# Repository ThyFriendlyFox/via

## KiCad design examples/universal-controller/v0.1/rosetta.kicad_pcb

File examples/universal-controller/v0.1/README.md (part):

# Rosetta v0.1: a universal game controller

Archived: [v0.2](../v0.2/README.md) is current. It is laid out like an Xbox 360 controller's main
board, with the thumbsticks, the Hall-effect triggers and the bumpers on it.

One controller for a PS4, a PS5, an Xbox, a Switch, or anything over Bluetooth. A 5-position
knob on its face picks the console. The controller drops off the bus while the knob turns and
comes back as the chosen console's own controller.

This folder is a whole KiCad 10 project made with Via: `design.py` is the board, and the
`.kicad_*` files beside it are what `workcenter design` writes from it. It is Via's example
project, laid out the way a board repository lays out a version.

<!-- pictures:begin -->

| Front | Back |
|---|---|
|  |  |

| Every layer | The schematic, wired, in blocks |
|---|---|
|  |  |

From `workcenter render . --strict --views schematic,3d,layers,spin --width 1600 --spin-zoom 1.1`, with
KiCad's 3D bodies in `KICAD10_3DMODEL_DIR` (Via's `site/media/README.md` says how to
fetch them) and the 3 bodies in `models/`.
<!-- pictures:end -->

## What is hard about it, and where each part lives

| The problem | The answer on this board |
|---|---|
| 1 knob, 5 consoles, no microcontroller pin to spare | SW1, an NKK NR01 1-pole 5-position rotary switch, taps a ladder of 6 x 1k (R40-R45). The ADC reads 1 number: position k at (6 - k)/6 of full scale. Between detents R46 (100k) pulls the wiper to ~0, and the firmware drops off the bus. 6 decks hold every position inside its window at every corner (`sim/`). |
| A PS4, a PS5 and an Xbox talk only to a licensed controller | J2 is a USB host port for an auth donor: a licensed controller or dongle. The RP2040 runs a second USB port in software (PIO-USB, GPIO16 and GPIO17, R7 to R10) and relays the console's challenge to the donor. U13 switches the port's 5 V and reports a fault. |
| Bluetooth Classic (the Switch, PlayStation pads) and BLE (phones, PCs) | U3, an ESP32-WROOM-32E, on the RP2040's UART0. The RP2040 holds its EN and IO0, so it can put the ESP32 in its bootloader and flash it: 1 USB cable updates both chips. U3 sits on the back, turned so its antenna hangs past the notch between the grips: the footprint's antenna keep-out lies in the air. |
| Sticks that drift | Hall-effect stick and trigger modules on J3 to J6, read by U4, a 12-bit 8-input SPI ADC (MCP3208) whose reference is the same +3V3 that feeds the sensors. |
| Triggers that push back (the PS5's trigger effects) | A small motor in each trigger module, on pins 4 and 5 of J3 and J4, driven both ways by U6 (DRV8833). |
| Rumble in each grip | An LRA on J7 and J8, each with a DRV2605L (U9, U10). The chip has 1 fixed I2C address, so each has its own bus (I2C0, I2C1). |
| Gyro aim | U5, an LSM6DSL 6-axis IMU on I2C0. |
| A light that names the console | 5 RGB LEDs (D2-D6, WS2812B-2020) on a ring round the knob. They need 3.7 V or more; they run from VSYS (the cell or USB), and U14 (74AHCT1G125) lifts the RP2040's 3.3 V data to that rail. |
| 16 buttons and 2 paddles | 2 74HC165 shift registers (U7, U8) on 3 pins, each input held up by a 10k in a pack (RN1-RN4). The back paddles SW15 and SW16 go to their own pins. |

## The board

- Outline: a controller's silhouette, 160 x 92 mm, drawn in `design.py` as a polygon with filleted
  corners (`ControllerDesign`). The notch between the grips is concave; its edge is where the
  ESP32's antenna hangs out.
- 4 layers, 1.6 mm: F.Cu signal, In1.Cu a whole GND plane, In2.Cu signal, B.Cu signal. Order it as
  4 layers.
- The front carries what a hand touches: the D-pad, A/B/X/Y, L1/R1, Share, Options, Home,
  Capture, the knob and its ring, and the connectors. The back carries the electronics and the
  2 paddles.
- 2 stick modules sit over the face at (147, 141) and (193, 141): `design.py` keeps every part on
  the front out of a 10 mm circle there (`d.keepout(..., parts=True, copper=False)`).

### Power

USB VBUS (J1) feeds VSYS through D1; with no cable, Q1 (AO3401A) connects the cell to VSYS. Its
gate sits on VBUS, held low by R13 when the cable is out. U11 (MCP73831) charges the cell at
500 mA (R12, 2k). U12 (AP7361C, 1 A) makes +3V3 from VSYS. The RP2040 makes its own +1V1. R14 and
R15 halve the cell's voltage for the ADC (channel 7).

### The RP2040's pins

| GPIO | Net | To |
|---|---|---|
| 0, 1 | ESP_RXD, ESP_TXD | U3 UART0 (pins 34, 35) |
| 2, 3 | ESP_EN, ESP_IO0 | U3 reset and boot strap, each pulled up (R20, R21) |
| 4, 5 | I2C0 | U5 IMU, U9 left haptics, R26/R27 |
| 6, 7 | I2C1 | U10 right haptics, R28/R29 |
| 8-11 | ADC_MISO, ADC_CS, ADC_SCK, ADC_MOSI | U4 (SPI1); R22 holds CS high in reset |
| 12, 13, 14 | SR_PL, SR_CLK, SR_Q | U7, U8 (R47, R48 hold the load and clock in reset) |
| 15 | LED_DATA | U14, then the ring (R49 holds it low in reset) |
| 16, 17 | PIO_D+, PIO_D- | J2 through R7, R8 (PIO-USB host; R9, R10 the host's pull-downs) |
| 18, 19 | HOST_EN, FAULT_N | U13 enable (R11 off in reset); U13's and U6's faults, wired-OR (R24) |
| 20-23 | TRIG_L_A/B, TRIG_R_A/B | U6 inputs, PWM slices 2 and 3 |
| 24 | MOT_SLEEP | U6 nSLEEP (R23 low in reset) |
| 25 | IMU_INT | U5 INT1 |
| 26 | HAPTIC_EN | U9, U10 EN (R25 low in reset) |
| 27, 28 | PADDLE_L, PADDLE_R | SW15, SW16 (internal pull-ups) |
| 29 | CHG_STAT | U11 STAT (internal pull-up) |

The ADC's channels: 0-3 the sticks' X and Y, 4 and 5 the triggers, 6 the knob, 7 the cell.

### Connectors

| Ref | Part | Pins |
|---|---|---|
| J1 | USB-C (GCT USB4085, through-hole) to the console | VBUS, D+/D- (R3, R4 27 ohm), CC1/CC2 5.1k to GND (a device) |
| J2 | USB-C to the auth donor | VBUS_HOST from U13, D+/D- to PIO-USB, CC1/CC2 56k to VBUS_HOST (a source) |
| J3, J4 | JST SH 5-way, left and right trigger modules | 1 +3V3, 2 Hall output, 3 GND, 4 and 5 the motor |
| J5, J6 | JST SH 5-way, left and right stick modules | 1 +3V3, 2 X, 3 Y, 4 the stick's click, 5 GND |
| J7, J8 | JST SH 2-way, the LRAs | 1 OUT+, 2 OUT- |
| J9 | JST PH 2-way, the cell | 1 BAT, 2 GND |
| J10 | JST SH 3-way, Raspberry Pi's debug connector, on the back | 1 SWCLK, 2 GND, 3 SWDIO |

## What proves it

```sh
workcenter design design.py --route    # the KiCad project, routed: from this folder
workcenter gates .                     # ERC, DRC, SIM, EXPORT
make -C firmware test                  # the knob's decoder on the host
```

- **The gates.** ERC and DRC on the routed board, the 6 knob decks at their corners, and the
  fabrication outputs in `build/fab/`. The site shows the run.
- **The knob, simulated.** `sim/mode_p1.cir` to `sim/mode_p5.cir` put the wiper on each tap and
  `sim/mode_between.cir` on none, each with the ADC's worst input leakage (1 uA). Every resistor
  runs at both ends of 1 % and 32 Monte Carlo draws (`sim/corners.json`). Each position stays
  within 0.04 of full scale of its nominal; the decoder's thresholds are 0.0833 away.
  The first value of R46 was 1 M: with that leakage it read 1 V between detents, a position.
  The deck found it; R46 is 100k and the ladder 1k.
- **The decoder.** `firmware/src/mode.c` turns a reading into a mode and decides when to drop off
  the bus and come back. `firmware/tests/test_mode.c` checks it against the decks' corner values:
  a brush past a tap changes nothing, and a fast flick detaches before it attaches.

## Parts and why

| Ref | Part | Why |
|---|---|---|
| U1 | RP2040, W25Q128JV (U2), 12 MHz (Y1) | Native USB for the console, PIO for a second USB port in software, 2 I2C, 2 UART, SPI, 16 PWM channels. |
| U3 | ESP32-WROOM-32E | Bluetooth Classic and BLE in 1 certified module. The ESP32-S3 has BLE only. |
| U4 | MCP3208 | 8 inputs at 12 bits on SPI, against an external reference. |
| U5 | LSM6DSL | A 6-axis IMU in KiCad's library, I2C. |
| U6 | DRV8833 | 2 H-bridges for the 2 trigger motors, from VSYS. |
| U9, U10 | DRV2605L | LRA drivers with a library of effects and auto-resonance. |
| U11 | MCP73831 | A 1-cell charger in SOT-23-5. |
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
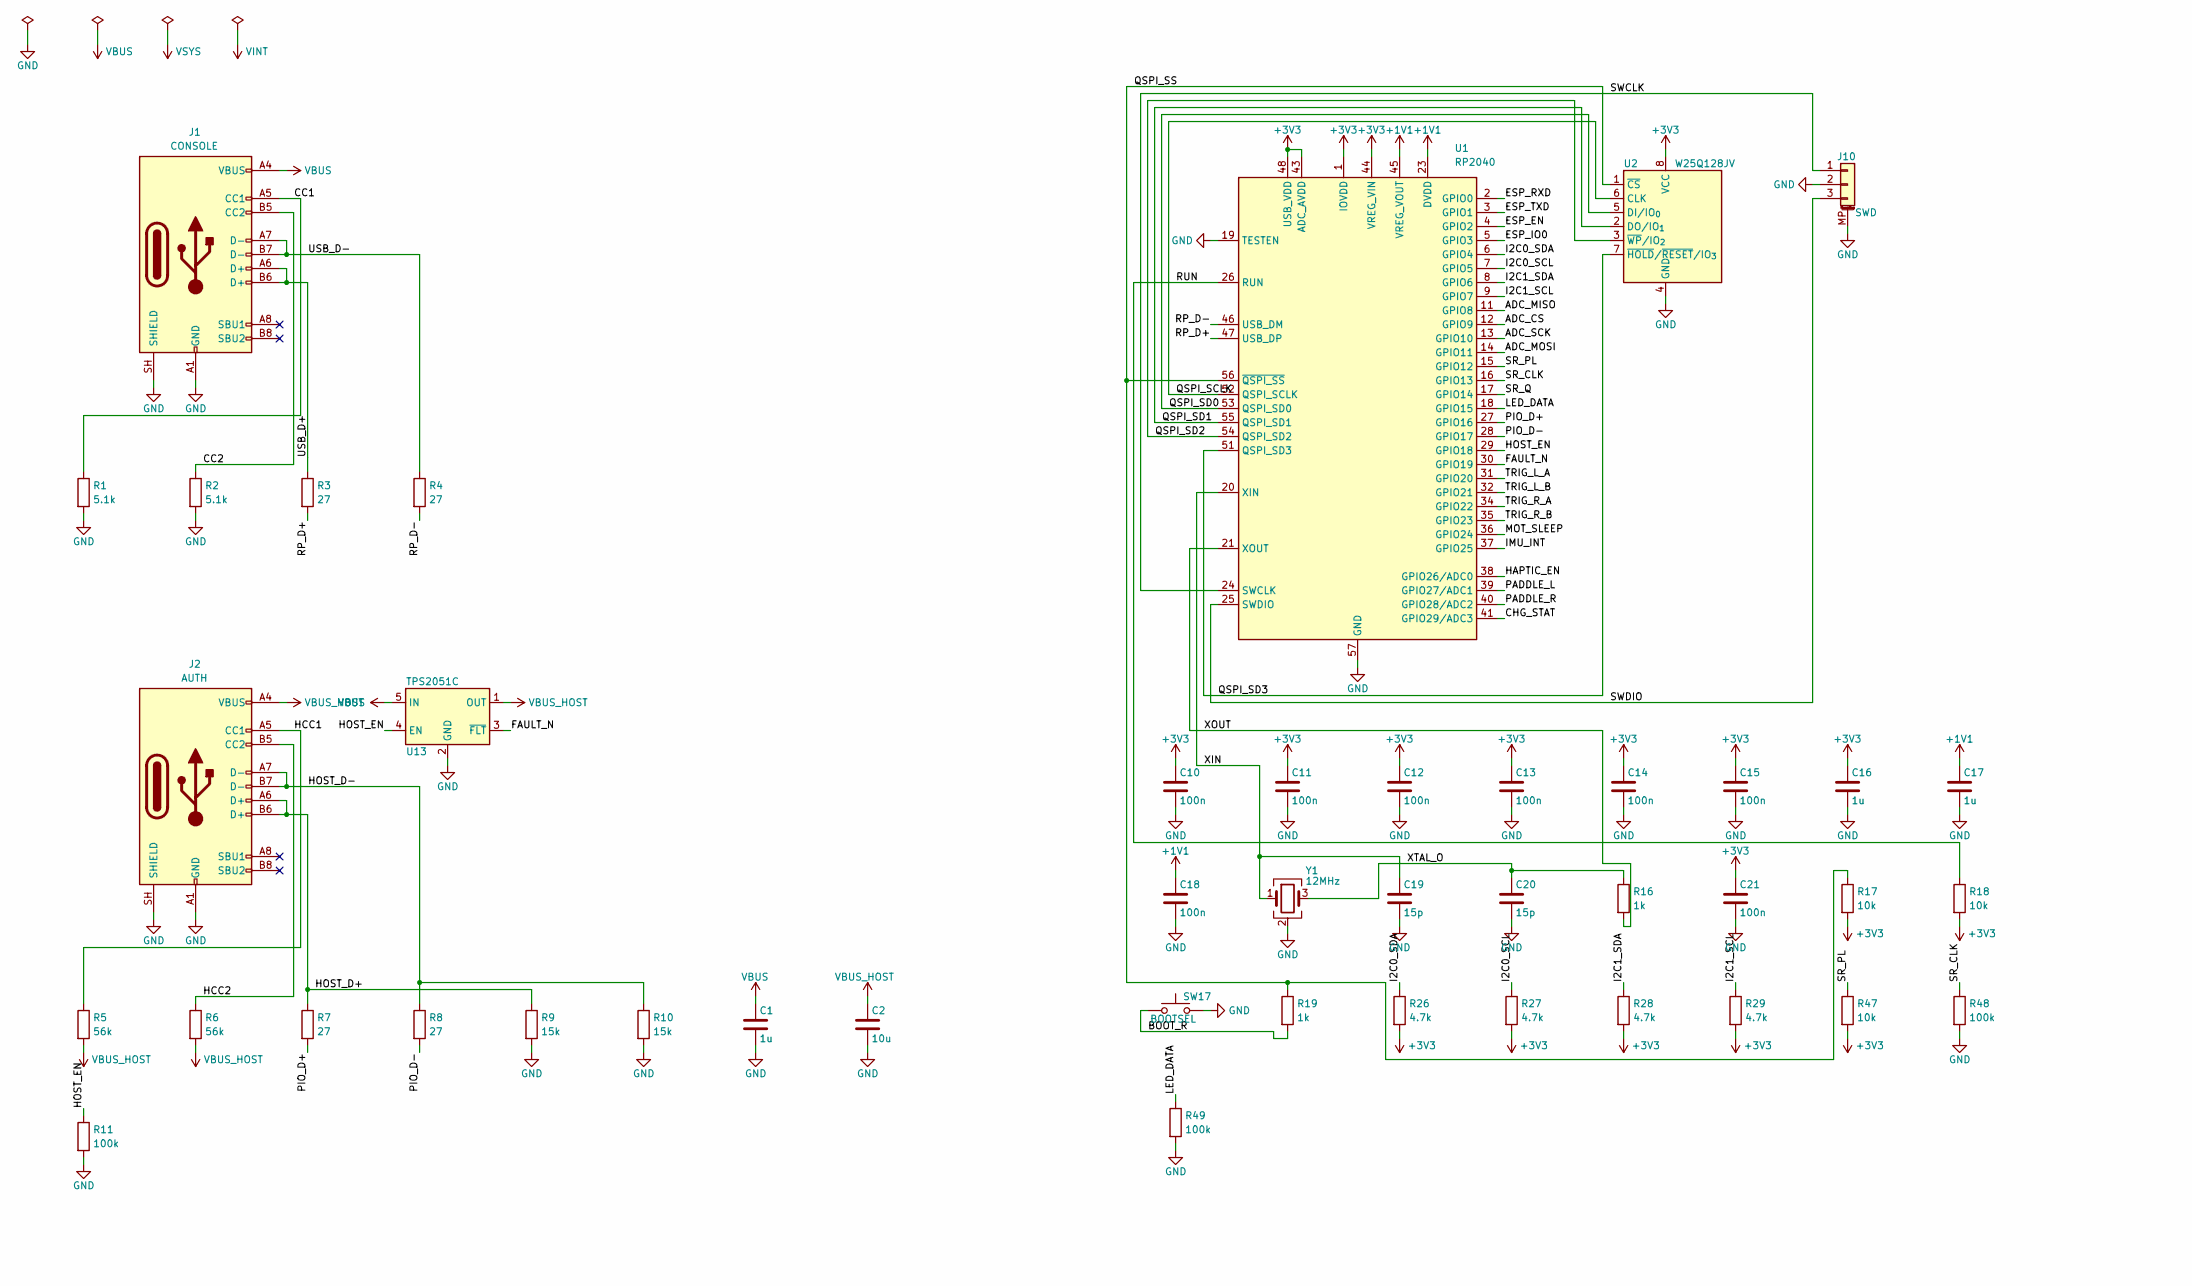
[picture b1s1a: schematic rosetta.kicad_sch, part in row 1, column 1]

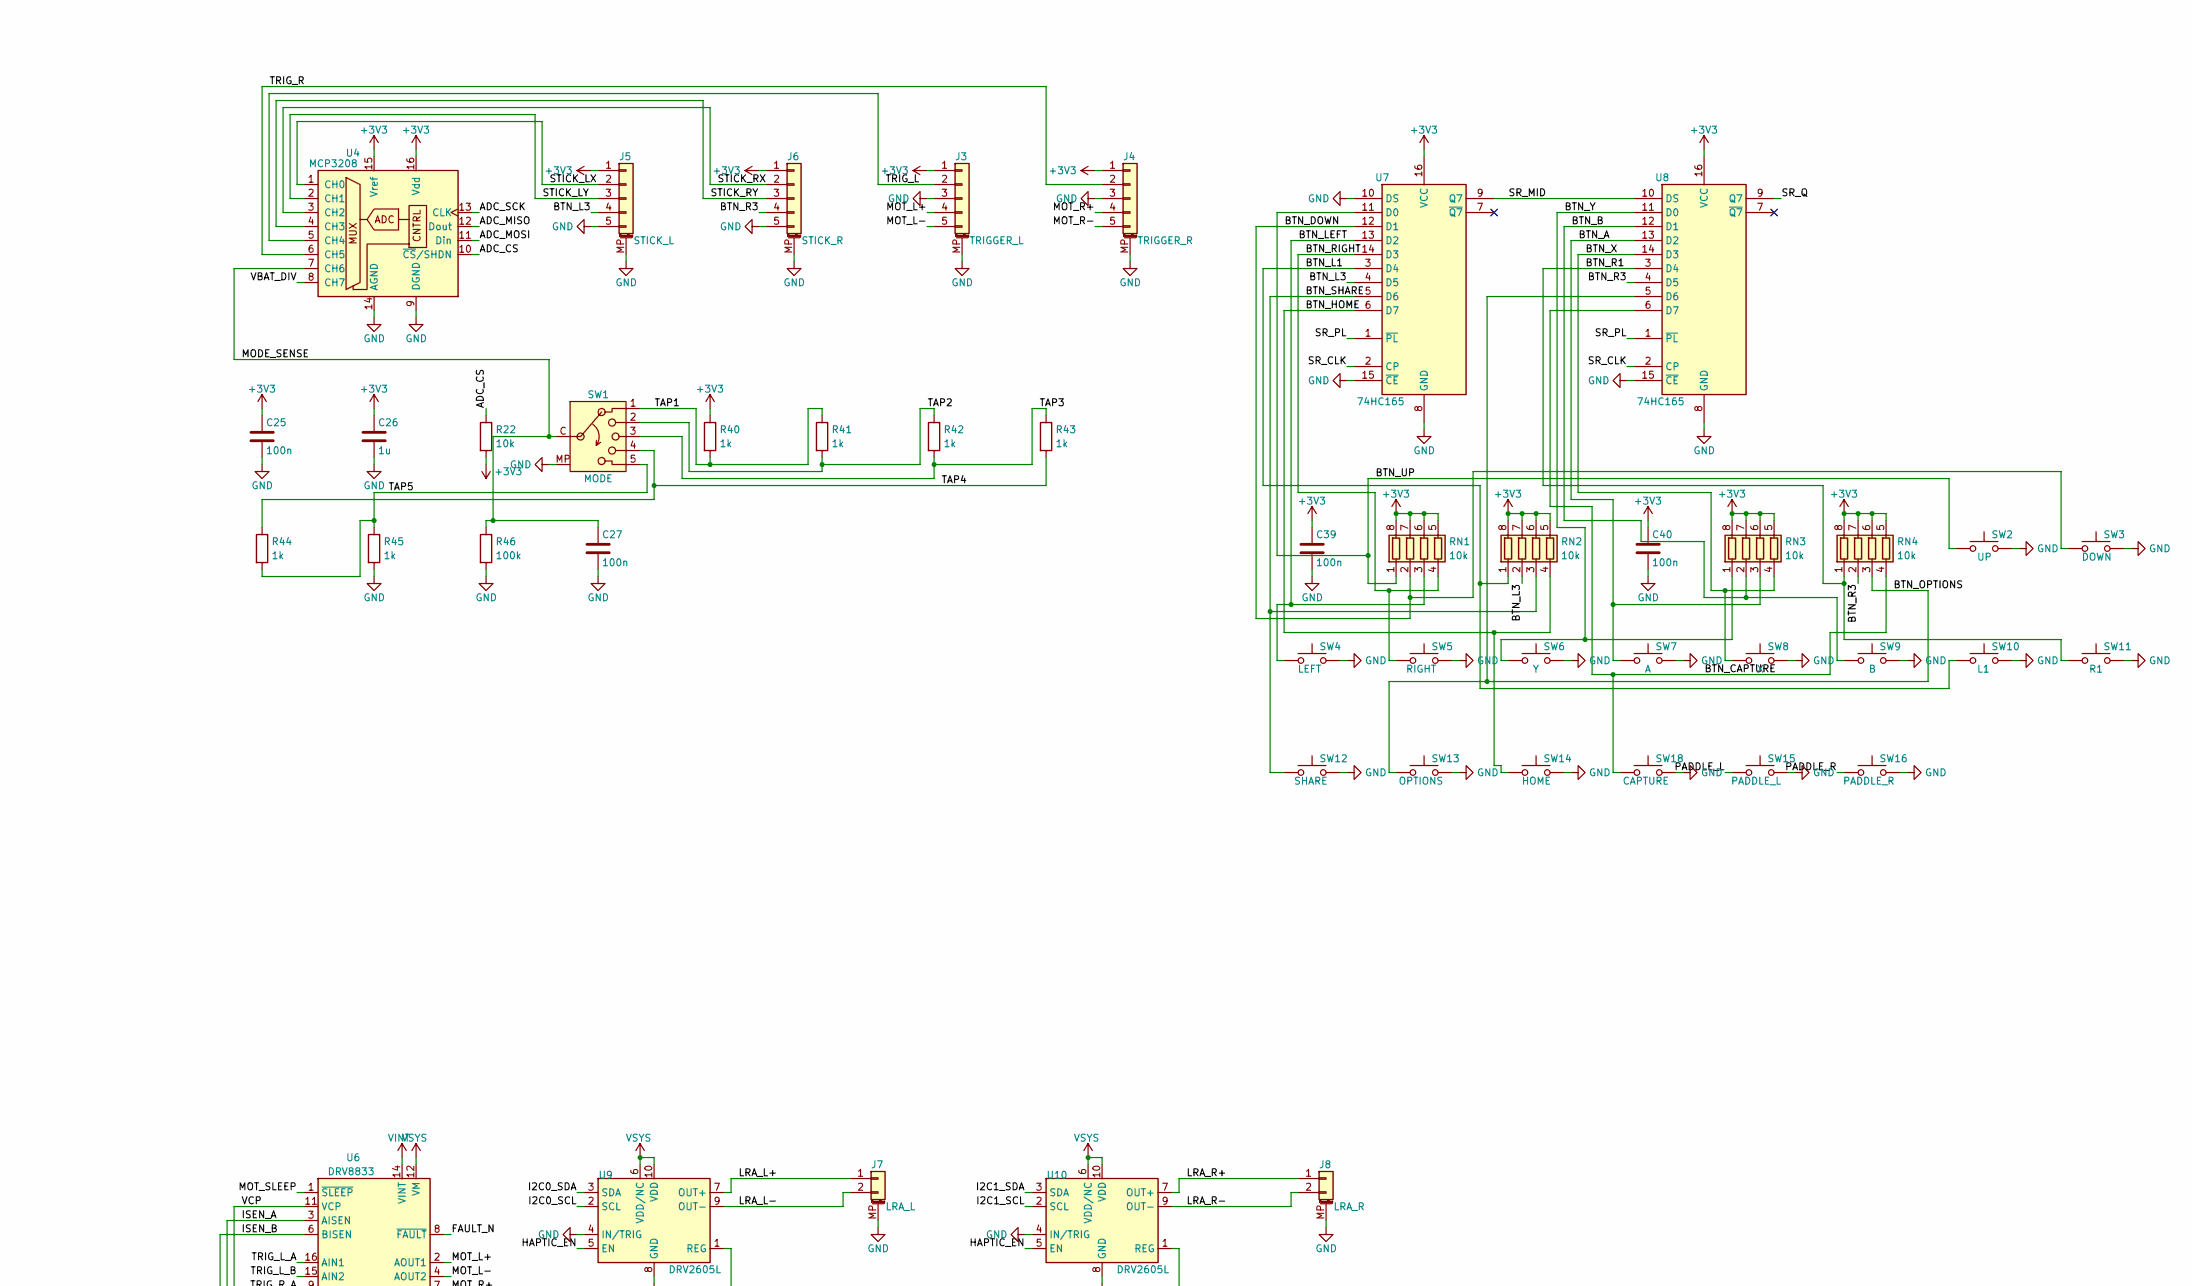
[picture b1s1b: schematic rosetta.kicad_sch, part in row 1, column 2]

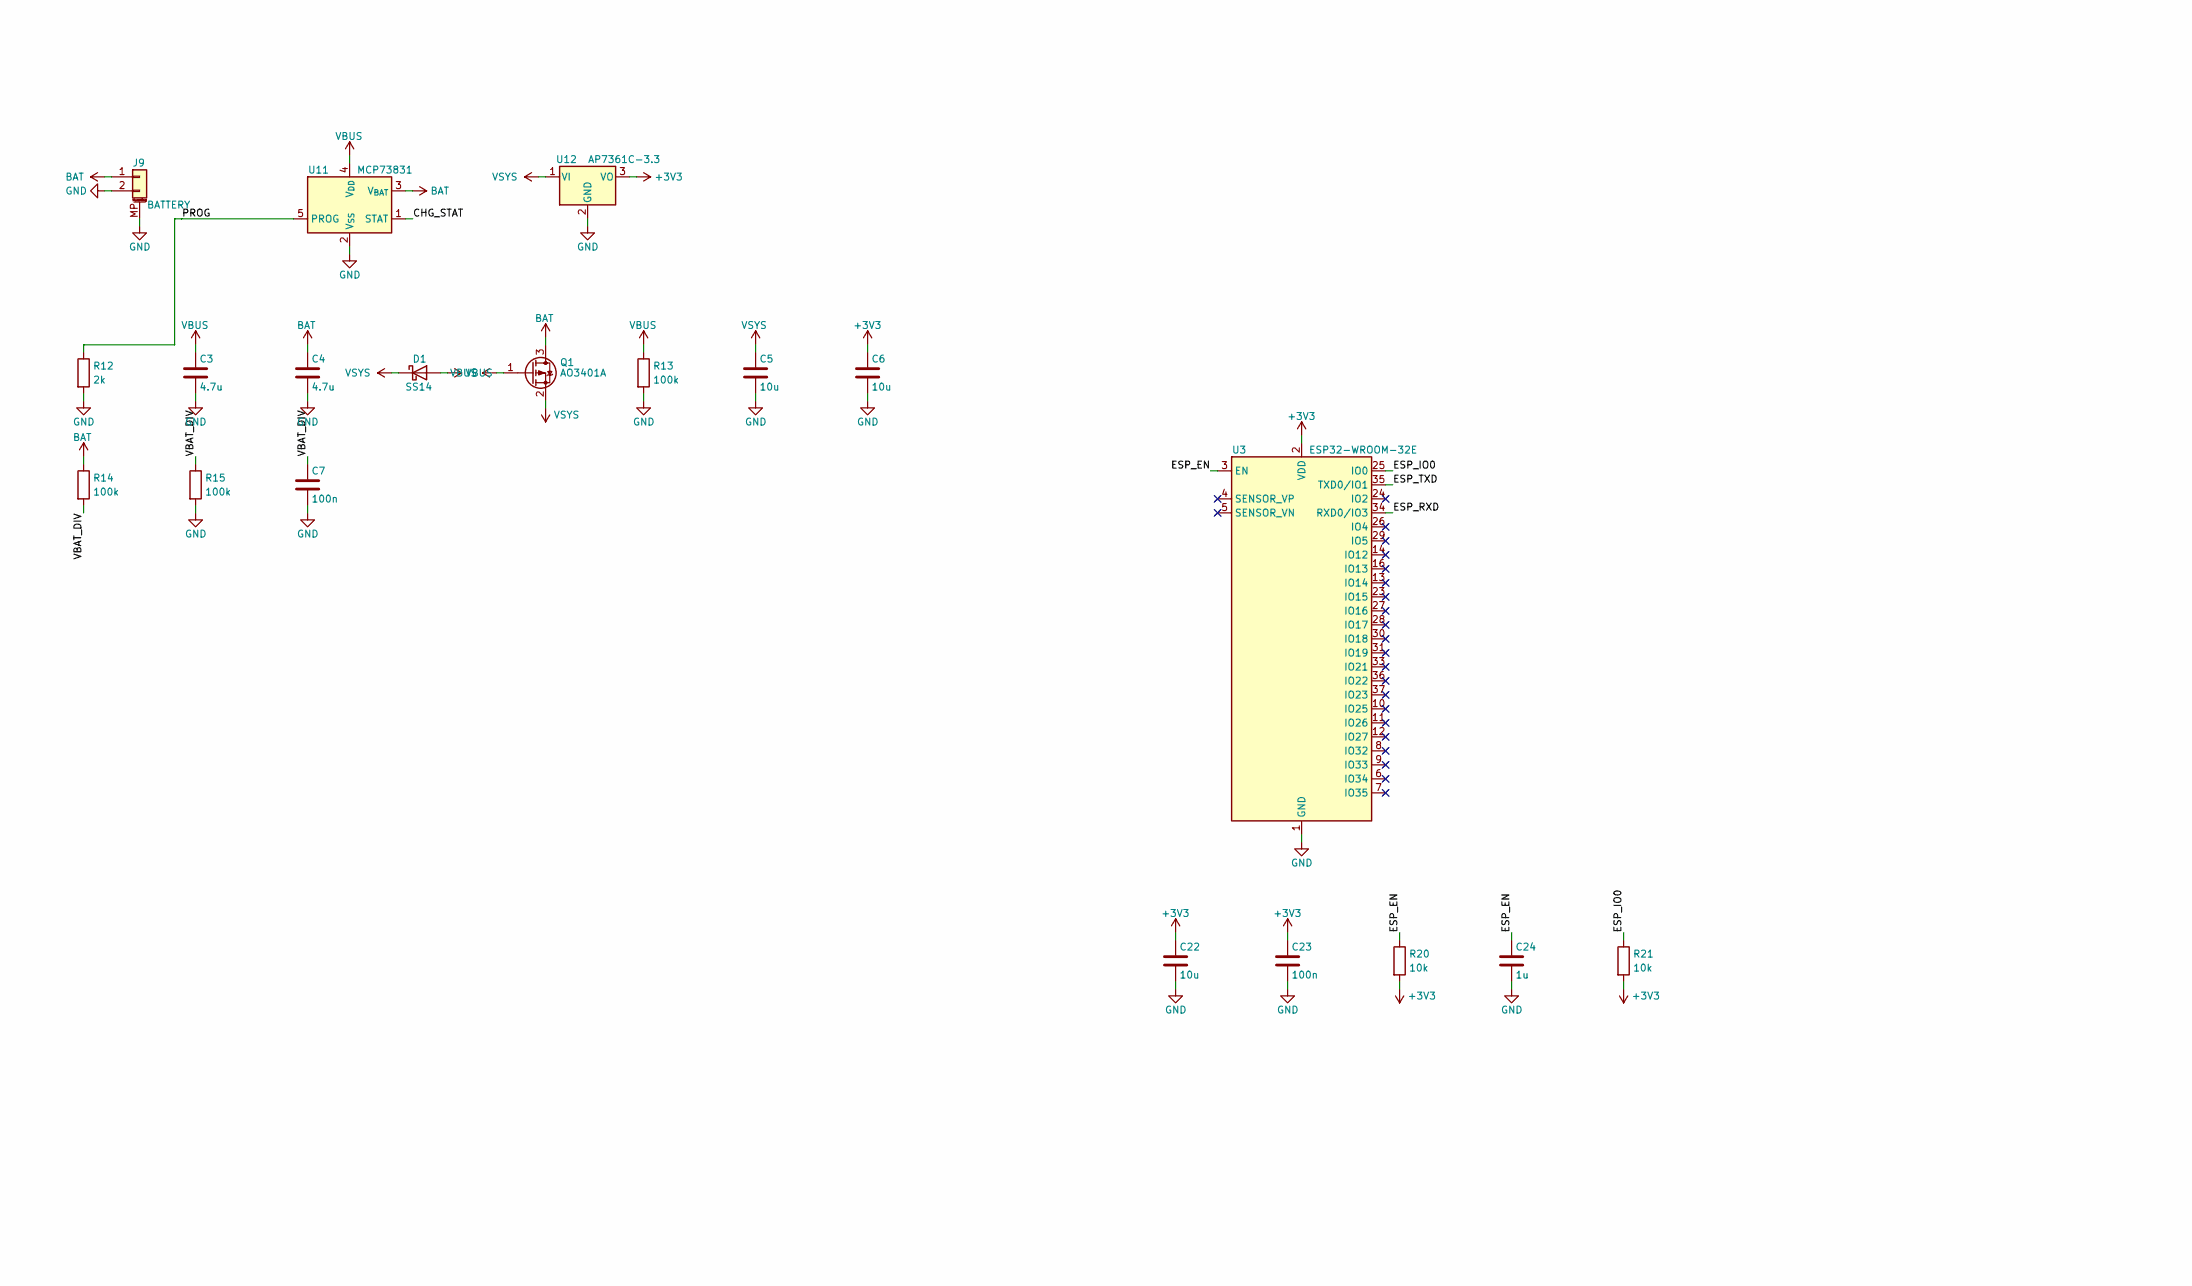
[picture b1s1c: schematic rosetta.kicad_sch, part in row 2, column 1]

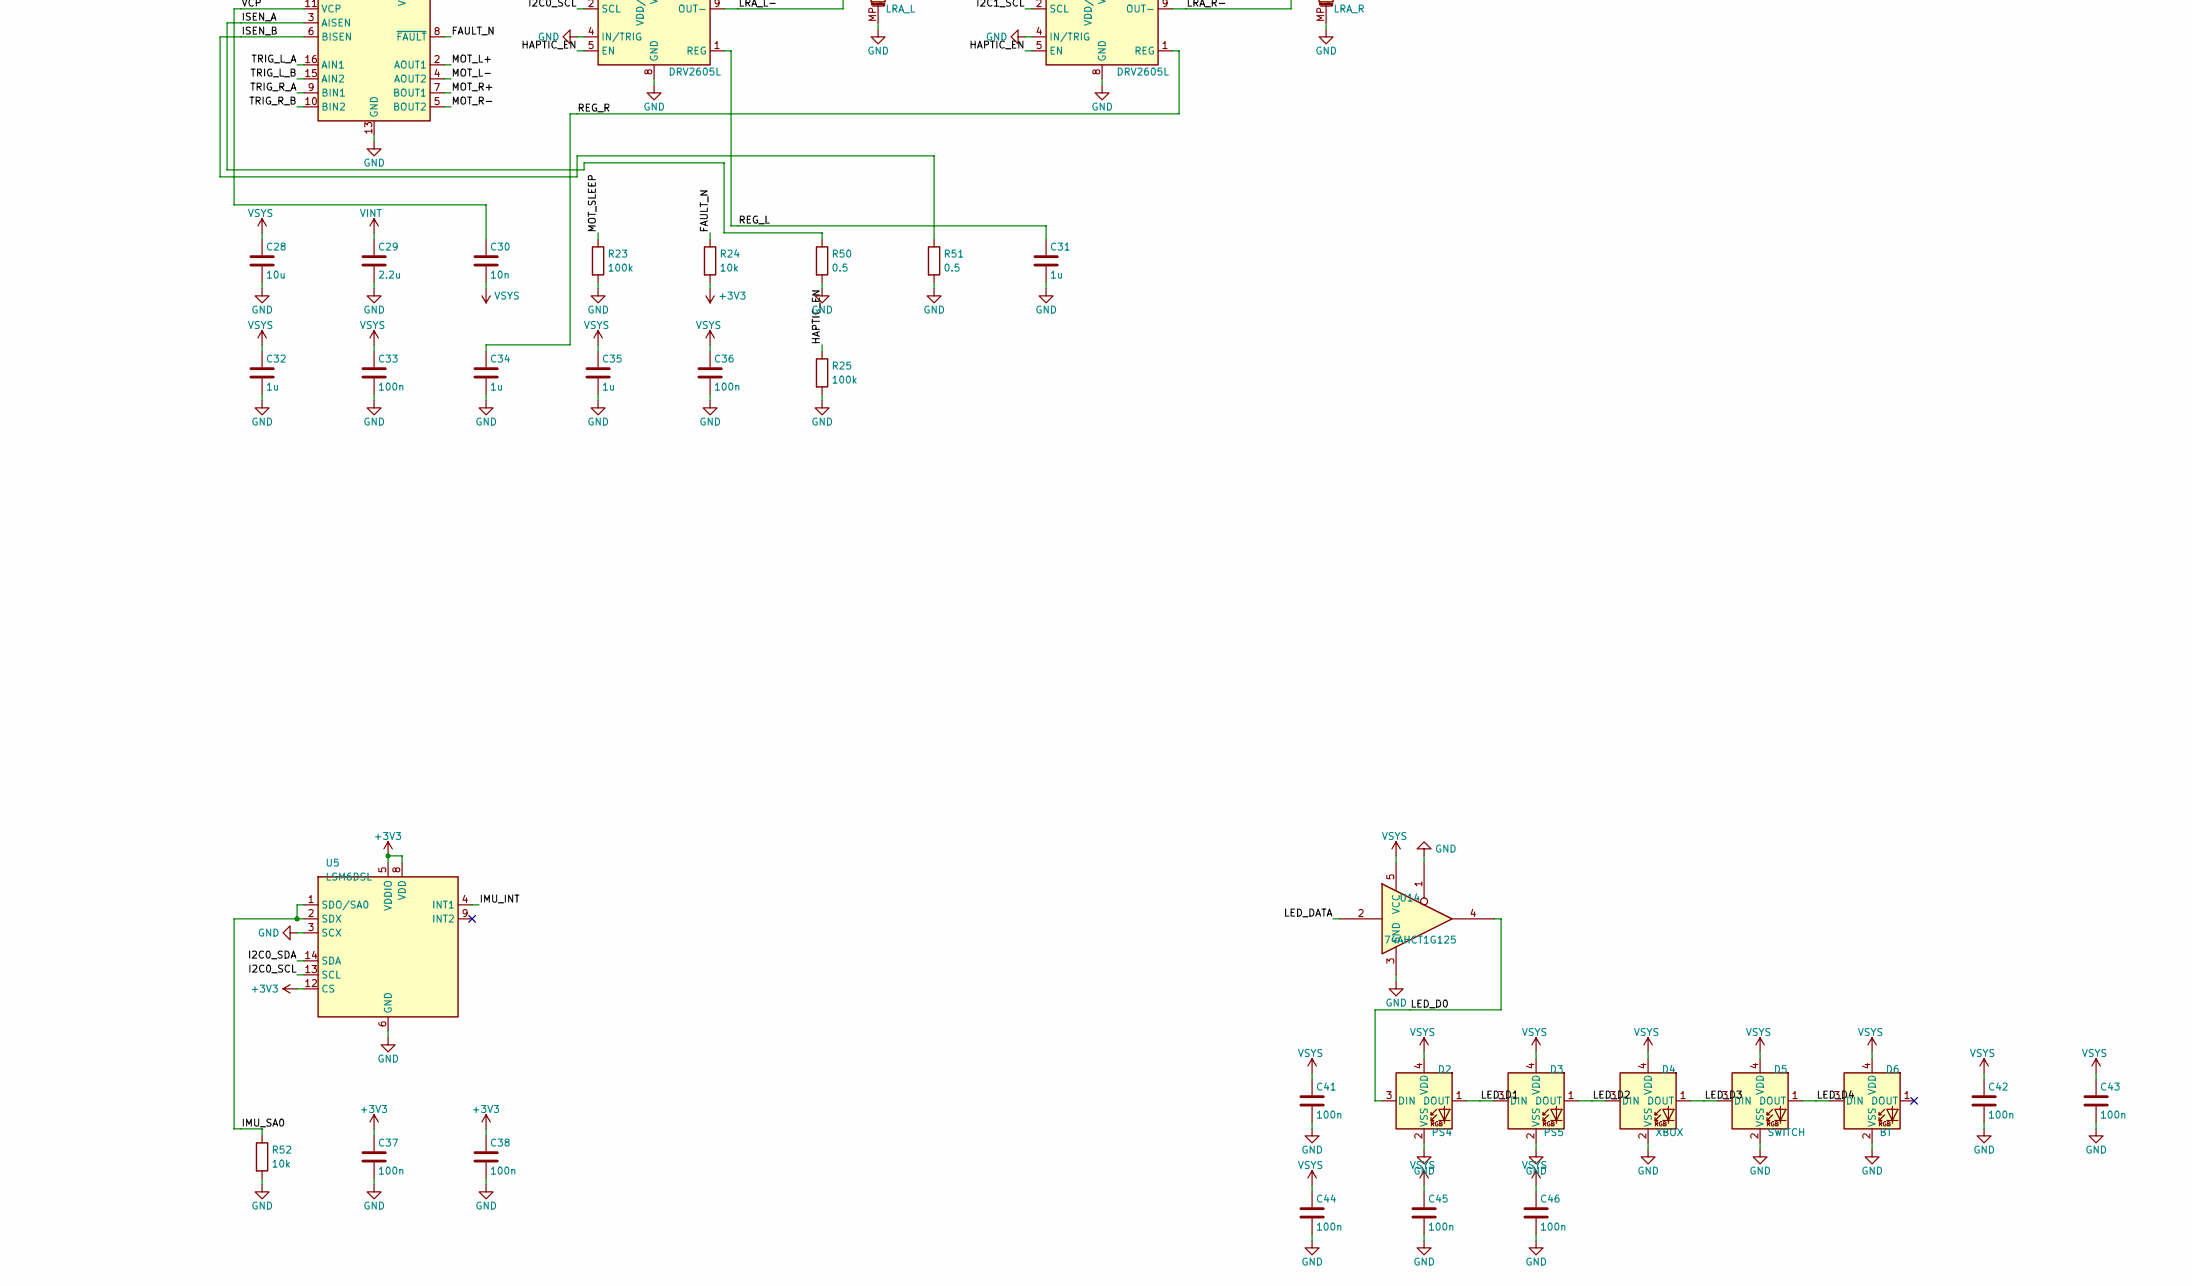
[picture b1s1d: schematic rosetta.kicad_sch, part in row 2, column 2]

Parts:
C1, C16, C17, C24, C26, C31, C32, C34, C35: 1u; C_0603_1608Metric
C2, C5, C6, C22, C28: 10u; C_0805_2012Metric
C3, C4: 4.7u; C_0805_2012Metric
C7, C10, C11, C12, C13, C14, C15, C18, C21, C23, C25, C27, C33, C36, C37, C38, C39, C40, C41, C42, C43, C44, C45, C46: 100n; C_0603_1608Metric
C19, C20: 15p; C_0603_1608Metric
C29: 2.2u; C_0603_1608Metric
C30: 10n; C_0603_1608Metric
D1: SS14; D_SOD-123
D2: PS4; LED_WS2812B-2020_PLCC4_2.0x2.0mm
D3: PS5; LED_WS2812B-2020_PLCC4_2.0x2.0mm
D4: XBOX; LED_WS2812B-2020_PLCC4_2.0x2.0mm
D5: SWITCH; LED_WS2812B-2020_PLCC4_2.0x2.0mm
D6: BT; LED_WS2812B-2020_PLCC4_2.0x2.0mm
J1: CONSOLE; USB_C_Receptacle_GCT_USB4085
J2: AUTH; USB_C_Receptacle_GCT_USB4085
J3: TRIGGER_L; JST_SH_SM05B-SRSS-TB_1x05-1MP_P1.00mm_Horizontal
J4: TRIGGER_R; JST_SH_SM05B-SRSS-TB_1x05-1MP_P1.00mm_Horizontal
J5: STICK_L; JST_SH_SM05B-SRSS-TB_1x05-1MP_P1.00mm_Horizontal
J6: STICK_R; JST_SH_SM05B-SRSS-TB_1x05-1MP_P1.00mm_Horizontal
J7: LRA_L; JST_SH_SM02B-SRSS-TB_1x02-1MP_P1.00mm_Horizontal
J8: LRA_R; JST_SH_SM02B-SRSS-TB_1x02-1MP_P1.00mm_Horizontal
J9: BATTERY; JST_PH_S2B-PH-SM4-TB_1x02-1MP_P2.00mm_Horizontal
J10: SWD; JST_SH_SM03B-SRSS-TB_1x03-1MP_P1.00mm_Horizontal
Q1: AO3401A; SOT-23
R1, R2: 5.1k; R_0603_1608Metric
R3, R4, R7, R8: 27; R_0603_1608Metric
R5, R6: 56k; R_0603_1608Metric
R9, R10: 15k; R_0603_1608Metric
R11, R13, R14, R15, R23, R25, R46, R48, R49: 100k; R_0603_1608Metric
R12: 2k; R_0603_1608Metric
R16, R19, R40, R41, R42, R43, R44, R45: 1k; R_0603_1608Metric
R17, R18, R20, R21, R22, R24, R47, R52: 10k; R_0603_1608Metric
R26, R27, R28, R29: 4.7k; R_0603_1608Metric
R50, R51: 0.5; R_0603_1608Metric
RN1, RN2, RN3, RN4: 10k; R_Array_Convex_4x0603
SW1: MODE; SW_NKK_NR01
SW2: UP; SW_SPST_TL3342
SW3: DOWN; SW_SPST_TL3342
SW4: LEFT; SW_SPST_TL3342
SW5: RIGHT; SW_SPST_TL3342
SW6: Y; SW_SPST_TL3342
SW7: A; SW_SPST_TL3342
SW8: X; SW_SPST_TL3342
SW9: B; SW_SPST_TL3342
SW10: L1; SW_SPST_TL3342
SW11: R1; SW_SPST_TL3342
SW12: SHARE; SW_SPST_PTS810
SW13: OPTIONS; SW_SPST_PTS810
SW14: HOME; SW_SPST_PTS810
SW15: PADDLE_L; SW_SPST_TL3342
SW16: PADDLE_R; SW_SPST_TL3342
SW17: BOOTSEL; SW_SPST_PTS810
SW18: CAPTURE; SW_SPST_PTS810
U1: RP2040; QFN-56-1EP_7x7mm_P0.4mm_EP3.2x3.2mm
U2: W25Q128JV; SOIC-8_5.3x5.3mm_P1.27mm
U3: ESP32-WROOM-32E
U4: MCP3208; SOIC-16_3.9x9.9mm_P1.27mm
U5: LSM6DSL; LGA-14_3x2.5mm_P0.5mm_LayoutBorder3x4y
U6: DRV8833; TSSOP-16_4.4x5mm_P0.65mm
U7, U8: 74HC165; SOIC-16_3.9x9.9mm_P1.27mm
U9, U10: DRV2605L; TSSOP-10_3x3mm_P0.5mm
U11: MCP73831; SOT-23-5
U12: AP7361C-3.3; SOT-223-3_TabPin2
U13: TPS2051C; SOT-23-5
U14: 74AHCT1G125; SOT-23-5
Y1: 12MHz; Crystal_SMD_3225-4Pin_3.2x2.5mm

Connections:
+1V1: C17.1, C18.1, U1.23 (DVDD), U1.45 (VREG_VOUT), U1.50 (DVDD)
+3V3: C6.1, C10.1, C11.1, C12.1, C13.1, C14.1, C15.1, C16.1, C21.1, C22.1, C23.1, C25.1, C26.1, C37.1, C38.1, C39.1, C40.1, J3.1, J4.1, J5.1, J6.1, R17.2, R18.2, R20.2, R21.2, R22.2, R24.2, R26.2, R27.2, R28.2, R29.2, R40.1, R47.2, RN1.5 (R4.2), RN1.6 (R3.2), RN1.7 (R2.2), RN1.8 (R1.2), RN2.5 (R4.2), RN2.6 (R3.2), RN2.7 (R2.2), RN2.8 (R1.2), RN3.5 (R4.2), RN3.6 (R3.2), RN3.7 (R2.2), RN3.8 (R1.2), RN4.5 (R4.2), RN4.6 (R3.2), RN4.7 (R2.2), RN4.8 (R1.2), U1.1 (IOVDD), U1.10 (IOVDD), U1.22 (IOVDD), U1.33 (IOVDD), U1.42 (IOVDD), U1.43 (ADC_AVDD), U1.44 (VREG_VIN), U1.48 (USB_VDD), U1.49 (IOVDD), U2.8 (VCC), U3.2 (VDD), U4.15 (Vref), U4.16 (Vdd), U5.5 (VDDIO), U5.8 (VDD), U5.12 (CS), U7.16 (VCC), U8.16 (VCC), U12.3 (VO)
/ADC_CS: R22.1, U1.12 (GPIO9), U4.10 (~CS/SHDN)
/ADC_MISO: U1.11 (GPIO8), U4.12 (Dout)
/ADC_MOSI: U1.14 (GPIO11), U4.11 (Din)
/ADC_SCK: U1.13 (GPIO10), U4.13 (CLK)
/BOOT_R: R19.2, SW17.1
/BTN_A: RN3.3 (R3.1), SW7.1, U8.13 (D2)
/BTN_B: RN3.2 (R2.1), SW9.1, U8.12 (D1)
/BTN_CAPTURE: RN4.4 (R4.1), SW18.1, U8.6 (D7)
/BTN_DOWN: RN1.2 (R2.1), SW3.1, U7.12 (D1)
/BTN_HOME: RN2.4 (R4.1), SW14.1, U7.6 (D7)
/BTN_L1: RN2.1 (R1.1), SW10.1, U7.3 (D4)
/BTN_L3: J5.4, RN2.2 (R2.1), U7.4 (D5)
/BTN_LEFT: RN1.3 (R3.1), SW4.1, U7.13 (D2)
/BTN_OPTIONS: RN4.3 (R3.1), SW13.1, U8.5 (D6)
/BTN_R1: RN4.1 (R1.1), SW11.1, U8.3 (D4)
/BTN_R3: J6.4, RN4.2 (R2.1), U8.4 (D5)
/BTN_RIGHT: RN1.4 (R4.1), SW5.1, U7.14 (D3)
/BTN_SHARE: RN2.3 (R3.1), SW12.1, U7.5 (D6)
/BTN_UP: RN1.1 (R1.1), SW2.1, U7.11 (D0)
/BTN_X: RN3.4 (R4.1), SW8.1, U8.14 (D3)
/BTN_Y: RN3.1 (R1.1), SW6.1, U8.11 (D0)
/CC1: J1.A5 (CC1), R1.1
/CC2: J1.B5 (CC2), R2.1
/CHG_STAT: U1.41 (GPIO29/ADC3), U11.1 (STAT)
/ESP_EN: C24.1, R20.1, U1.4 (GPIO2), U3.3 (EN)
/ESP_IO0: R21.1, U1.5 (GPIO3), U3.25 (IO0)
/ESP_RXD: U1.2 (GPIO0), U3.34 (RXD0/IO3)
/ESP_TXD: U1.3 (GPIO1), U3.35 (TXD0/IO1)
/FAULT_N: R24.1, U1.30 (GPIO19), U6.8 (~FAULT), U13.3 (~FLT)
/HAPTIC_EN: R25.1, U1.38 (GPIO26/ADC0), U9.5 (EN), U10.5 (EN)
/HCC1: J2.A5 (CC1), R5.1
/HCC2: J2.B5 (CC2), R6.1
/HOST_D+: J2.A6 (D+), J2.B6 (D+), R7.1, R9.1
/HOST_D-: J2.A7 (D-), J2.B7 (D-), R8.1, R10.1
/HOST_EN: R11.1, U1.29 (GPIO18), U13.4 (EN)
/I2C0_SCL: R27.1, U1.7 (GPIO5), U5.13 (SCL), U9.2 (SCL)
/I2C0_SDA: R26.1, U1.6 (GPIO4), U5.14 (SDA), U9.3 (SDA)
/I2C1_SCL: R29.1, U1.9 (GPIO7), U10.2 (SCL)
/I2C1_SDA: R28.1, U1.8 (GPIO6), U10.3 (SDA)
/IMU_INT: U1.37 (GPIO25), U5.4 (INT1)
/IMU_SA0: R52.1, U5.1 (SDO/SA0), U5.2 (SDX)
/ISEN_A: R50.1, U6.3 (AISEN)
/ISEN_B: R51.1, U6.6 (BISEN)
/LED_D0: D2.3 (DIN), U14.4
/LED_D1: D2.1 (DOUT), D3.3 (DIN)
/LED_D2: D3.1 (DOUT), D4.3 (DIN)
/LED_D3: D4.1 (DOUT), D5.3 (DIN)
/LED_D4: D5.1 (DOUT), D6.3 (DIN)
/LED_DATA: R49.1, U1.18 (GPIO15), U14.2
/LRA_L+: J7.1, U9.7 (OUT+)
/LRA_L-: J7.2, U9.9 (OUT-)
/LRA_R+: J8.1, U10.7 (OUT+)
/LRA_R-: J8.2, U10.9 (OUT-)
/MODE_SENSE: C27.1, R46.1, SW1.C (Common), U4.7 (CH6)
/MOT_L+: J3.4, U6.2 (AOUT1)
/MOT_L-: J3.5, U6.4 (AOUT2)
/MOT_R+: J4.4, U6.7 (BOUT1)
/MOT_R-: J4.5, U6.5 (BOUT2)
/MOT_SLEEP: R23.1, U1.36 (GPIO24), U6.1 (~SLEEP)
/PADDLE_L: SW15.1, U1.39 (GPIO27/ADC1)
/PADDLE_R: SW16.1, U1.40 (GPIO28/ADC2)
/PIO_D+: R7.2, U1.27 (GPIO16)
/PIO_D-: R8.2, U1.28 (GPIO17)
/PROG: R12.1, U11.5 (PROG)
/QSPI_SCLK: U1.52 (QSPI_SCLK), U2.6 (CLK)
/QSPI_SD0: U1.53 (QSPI_SD0), U2.5 (DI/IO_{0})
/QSPI_SD1: U1.55 (QSPI_SD1), U2.2 (DO/IO_{1})
/QSPI_SD2: U1.54 (QSPI_SD2), U2.3 (~WP/IO_{2})
/QSPI_SD3: U1.51 (QSPI_SD3), U2.7 (~HOLD/~RESET/IO_{3})
/QSPI_SS: R17.1, R19.1, U1.56 (~QSPI_SS), U2.1 (~CS)
/REG_L: C31.1, U9.1 (REG)
/REG_R: C34.1, U10.1 (REG)
/RP_D+: R3.2, U1.47 (USB_DP)
/RP_D-: R4.2, U1.46 (USB_DM)
/RUN: R18.1, U1.26 (RUN)
/SR_CLK: R48.1, U1.16 (GPIO13), U7.2 (CP), U8.2 (CP)
/SR_MID: U7.9 (Q7), U8.10 (DS)
/SR_PL: R47.1, U1.15 (GPIO12), U7.1 (~PL), U8.1 (~PL)
/SR_Q: U1.17 (GPIO14), U8.9 (Q7)
/STICK_LX: J5.2, U4.1 (CH0)
/STICK_LY: J5.3, U4.2 (CH1)
/STICK_RX: J6.2, U4.3 (CH2)
/STICK_RY: J6.3, U4.4 (CH3)
/SWCLK: J10.1, U1.24 (SWCLK)
/SWDIO: J10.3, U1.25 (SWDIO)
/TAP1: R40.2, R41.1, SW1.1
/TAP2: R41.2, R42.1, SW1.2
/TAP3: R42.2, R43.1, SW1.3
/TAP4: R43.2, R44.1, SW1.4
/TAP5: R44.2, R45.1, SW1.5
/TRIG_L: J3.2, U4.5 (CH4)
/TRIG_L_A: U1.31 (GPIO20), U6.16 (AIN1)
/TRIG_L_B: U1.32 (GPIO21), U6.15 (AIN2)
/TRIG_R: J4.2, U4.6 (CH5)
/TRIG_R_A: U1.34 (GPIO22), U6.9 (BIN1)
/TRIG_R_B: U1.35 (GPIO23), U6.10 (BIN2)
/USB_D+: J1.A6 (D+), J1.B6 (D+), R3.1
/USB_D-: J1.A7 (D-), J1.B7 (D-), R4.1
/VBAT_DIV: C7.1, R14.2, R15.1, U4.8 (CH7)
/VCP: C30.1, U6.11 (VCP)
/XIN: C19.1, U1.20 (XIN), Y1.1
/XOUT: R16.2, U1.21 (XOUT)
/XTAL_O: C20.1, R16.1, Y1.3
BAT: C4.1, J9.1, Q1.3 (D), R14.1, U11.3 (V_{BAT})
GND: C1.2, C2.2, C3.2, C4.2, C5.2, C6.2, C7.2, C10.2, C11.2, C12.2, C13.2, C14.2, C15.2, C16.2, C17.2, C18.2, C19.2, C20.2, C21.2, C22.2, C23.2, C24.2, C25.2, C26.2, C27.2, C28.2, C29.2, C31.2, C32.2, C33.2, C34.2, C35.2, C36.2, C37.2, C38.2, C39.2, C40.2, C41.2, C42.2, C43.2, C44.2, C45.2, C46.2, D2.2 (VSS), D3.2 (VSS), D4.2 (VSS), D5.2 (VSS), D6.2 (VSS), J1.A1 (GND), J1.A12 (GND), J1.B1 (GND), J1.B12 (GND), J1.SH (SHIELD), J2.A1 (GND), J2.A12 (GND), J2.B1 (GND), J2.B12 (GND), J2.SH (SHIELD), J3.3, J3.MP (MountPin), J4.3, J4.MP (MountPin), J5.5, J5.MP (MountPin), J6.5, J6.MP (MountPin), J7.MP (MountPin), J8.MP (MountPin), J9.2, J9.MP (MountPin), J10.2, J10.MP (MountPin), R1.2, R2.2, R9.2, R10.2, R11.2, R12.2, R13.2, R15.2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
VBUS: C1.1, C3.1, D1.2 (A), J1.A4 (VBUS), J1.A9 (VBUS), J1.B4 (VBUS), J1.B9 (VBUS), Q1.1 (G), R13.1, U11.4 (V_{DD}), U13.5 (IN)
VBUS_HOST: C2.1, J2.A4 (VBUS), J2.A9 (VBUS), J2.B4 (VBUS), J2.B9 (VBUS), R5.2, R6.2, U13.1 (OUT)
VINT: C29.1, U6.14 (VINT)
VSYS: C5.1, C28.1, C30.2, C32.1, C33.1, C35.1, C36.1, C41.1, C42.1, C43.1, C44.1, C45.1, C46.1, D1.1 (K), D2.4 (VDD), D3.4 (VDD), D4.4 (VDD), D5.4 (VDD), D6.4 (VDD), Q1.2 (S), U6.12 (VM), U9.6 (VDD/NC), U9.10 (VDD), U10.6 (VDD/NC), U10.10 (VDD), U12.1 (VI), U14.5 (VCC)

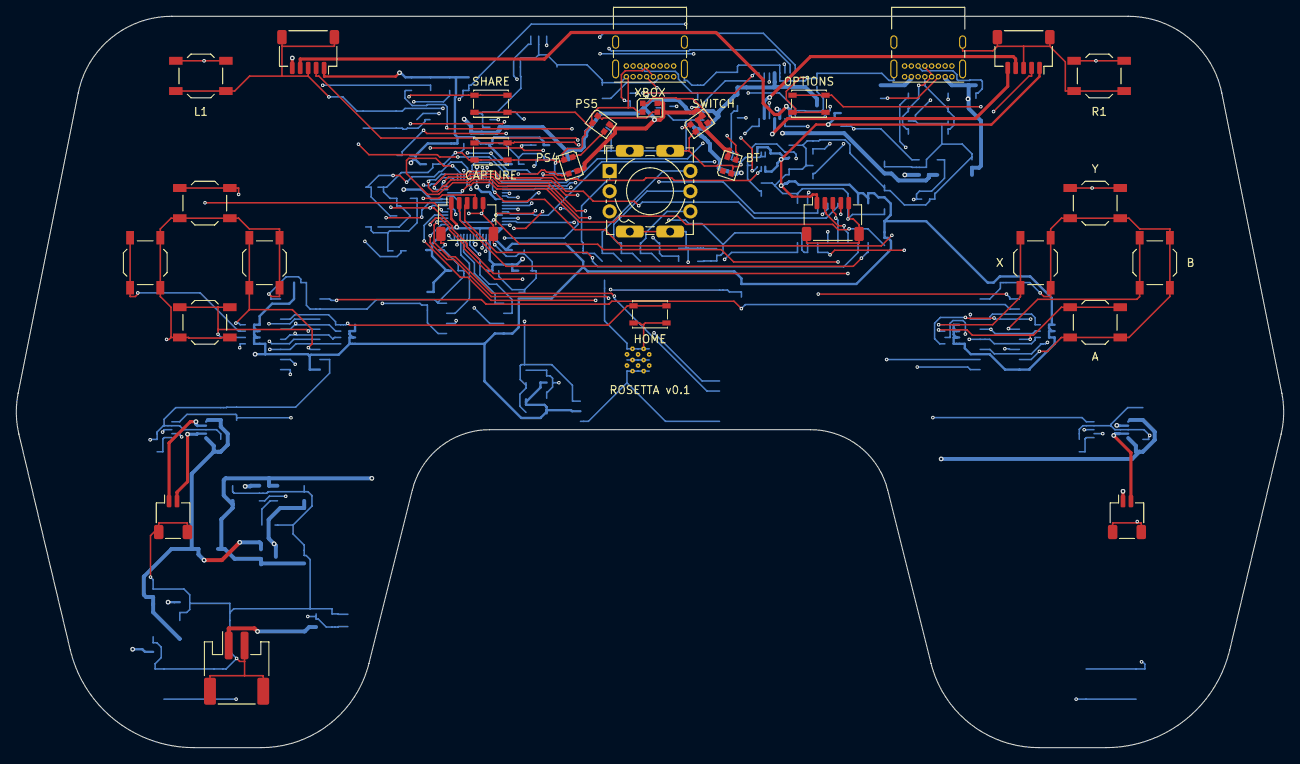
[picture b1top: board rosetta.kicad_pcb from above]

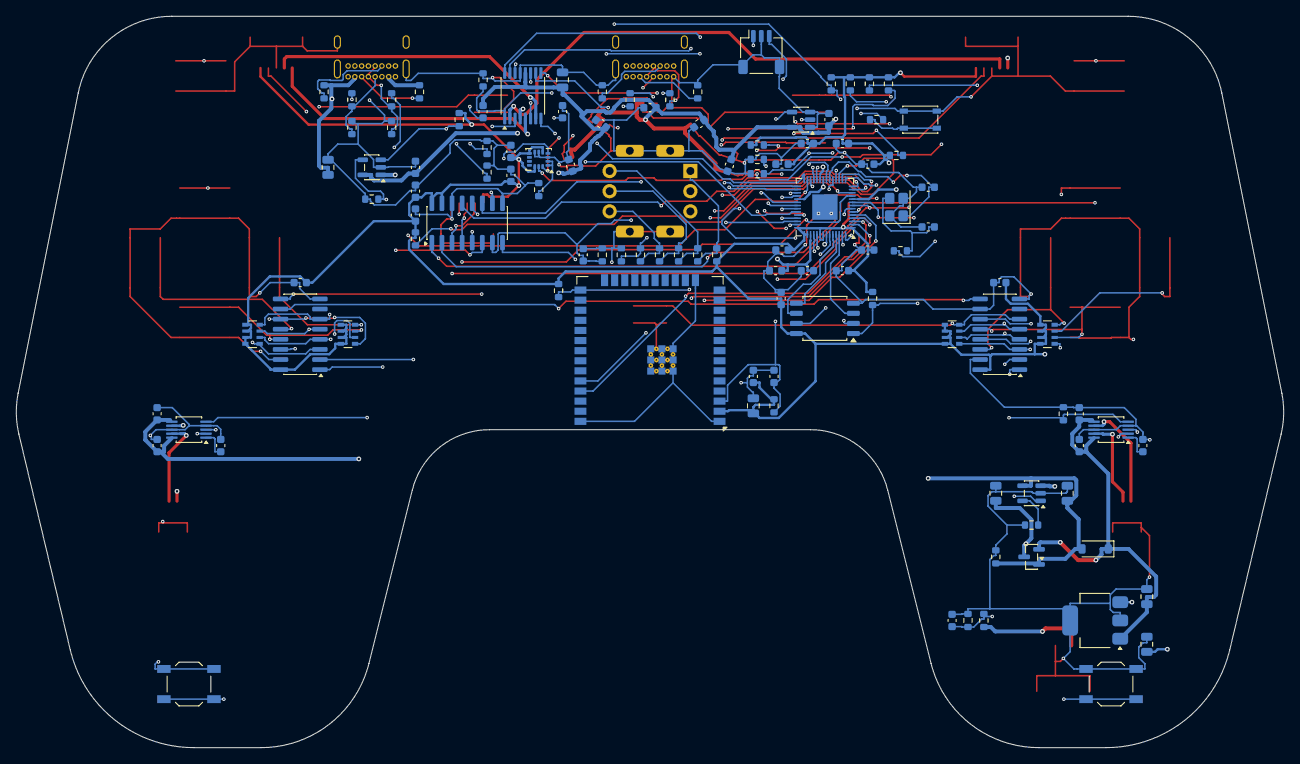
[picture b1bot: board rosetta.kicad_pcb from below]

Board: 4 copper layers, 159.4 x 92.0 mm, 140 parts (111 on the bottom side), 111 nets.

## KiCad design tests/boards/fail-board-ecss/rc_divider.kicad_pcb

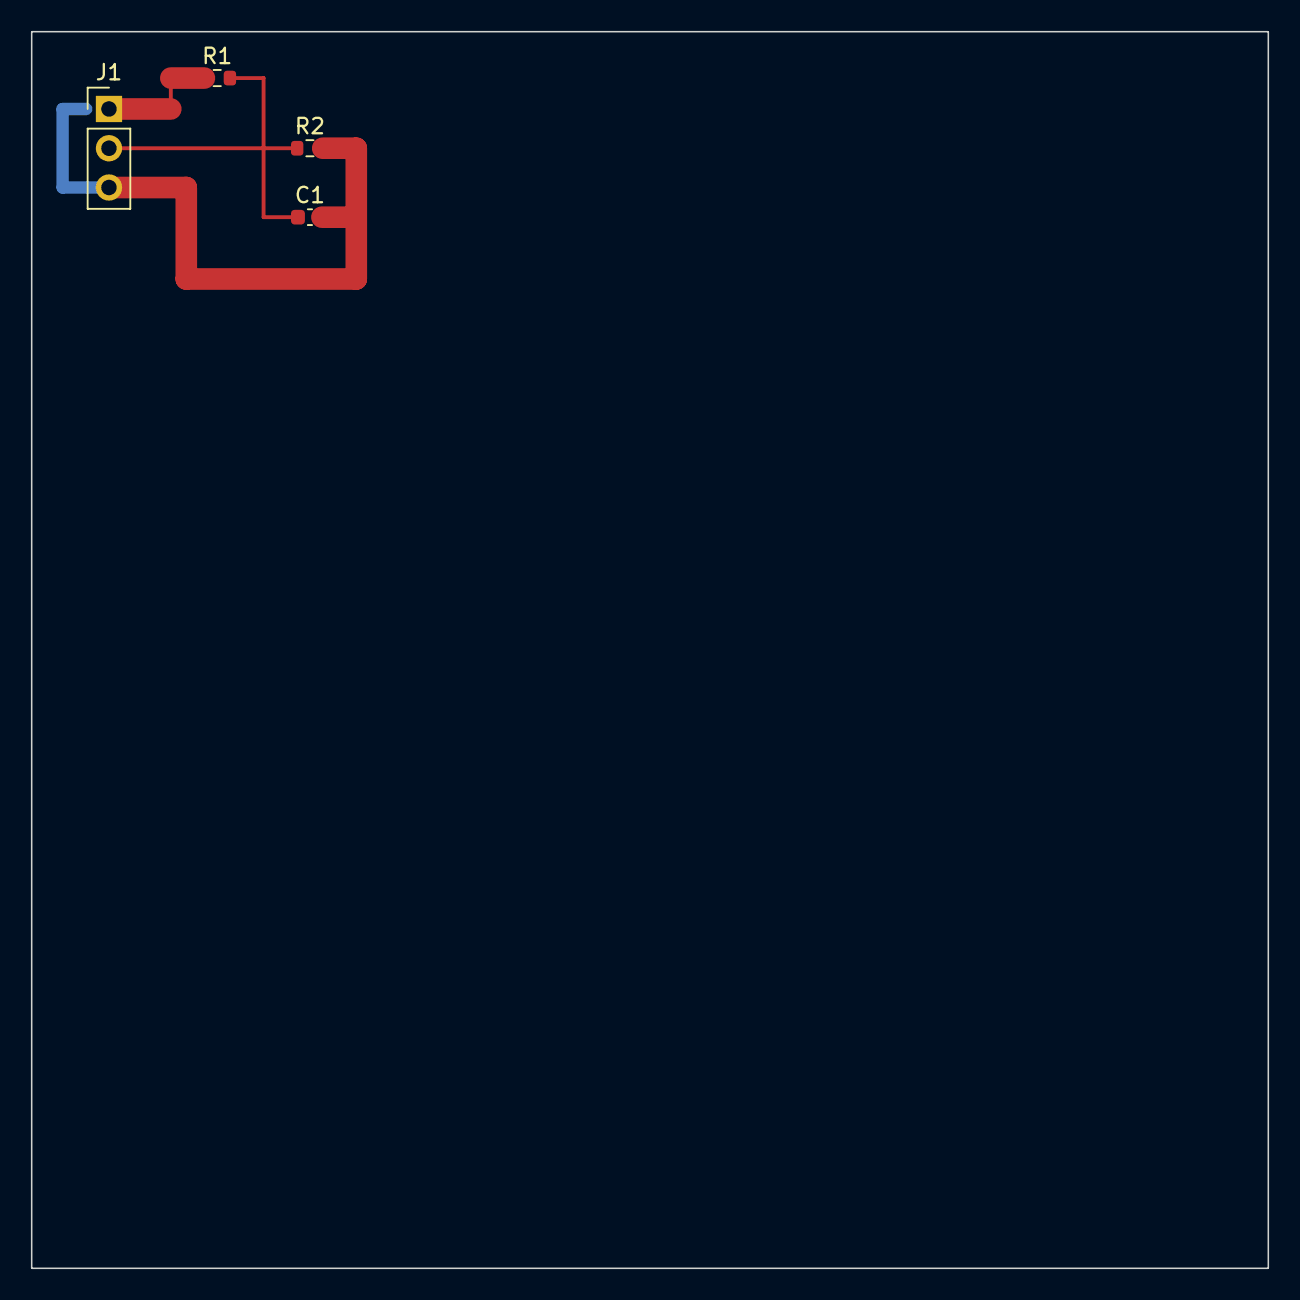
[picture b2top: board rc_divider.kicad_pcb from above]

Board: 2 copper layers, 80.0 x 80.0 mm, 4 parts (0 on the bottom side), 3 nets.

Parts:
C1: 100n; C_0603_1608Metric
J1: Conn_01x03; PinHeader_1x03_P2.54mm_Vertical
R1, R2: 10k; R_0603_1608Metric

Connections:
/GND: C1.2, J1.3, R2.2
/VIN: J1.1, R1.1
/VOUT: C1.1, J1.2, R1.2, R2.1
